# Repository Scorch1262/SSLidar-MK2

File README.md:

# SSLidar-MK2
Solid State Lidar

 Funktionen (Software V1.0) [F]:
	( Ab Board V2.0 )
- MCC UART1 Funktion
- MCC I2C Funktion
- MCC SPI Funktion
- MCC Fatfs Funktion
- Sensorauswertung 8x Time-of-Flight (VL53L0X)
- Speicherung der Sensordaten auf der SD-Karte
- Weitergabe/Verteilung von UART Signalen

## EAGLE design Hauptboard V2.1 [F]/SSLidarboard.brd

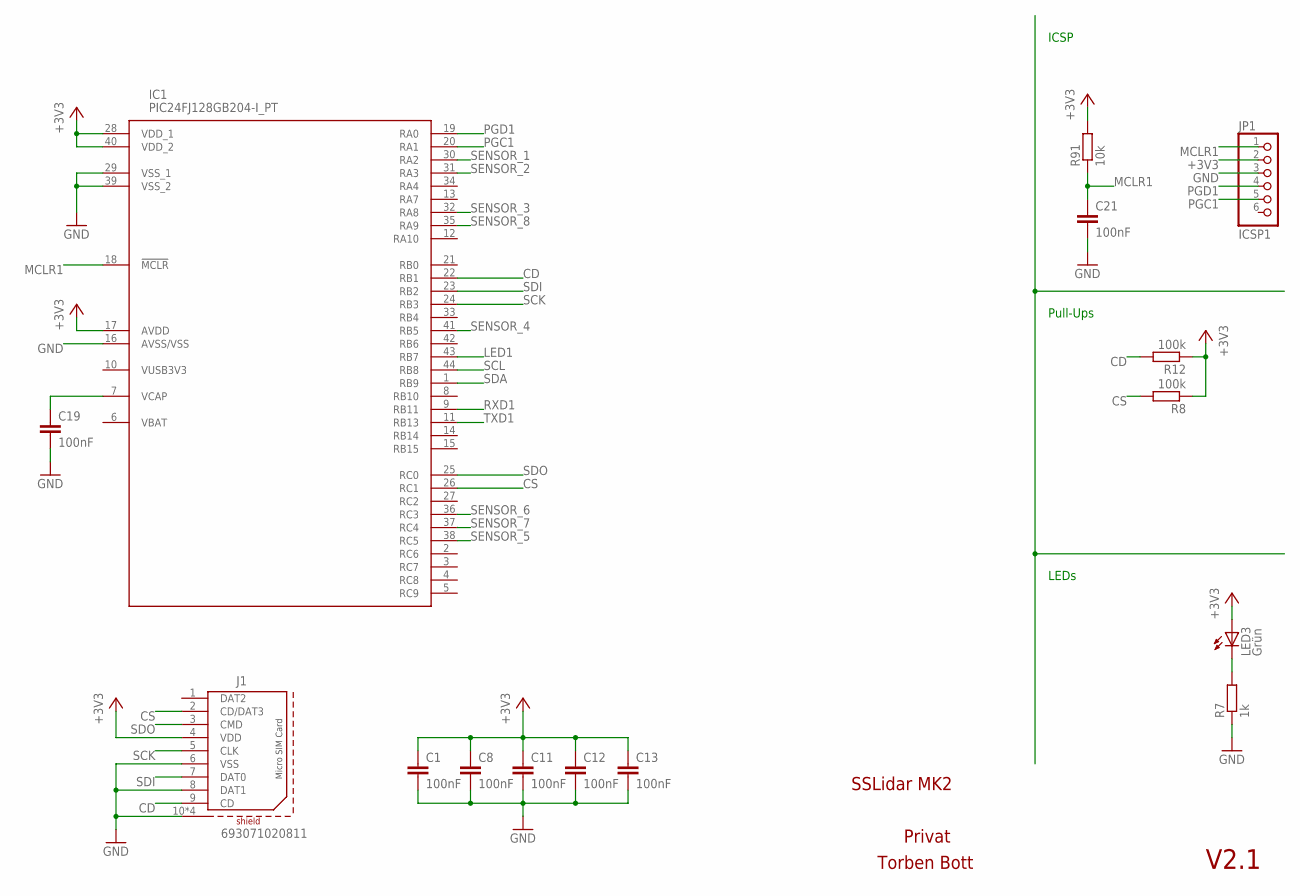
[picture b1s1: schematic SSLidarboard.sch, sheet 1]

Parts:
C1, C8, C11, C12, C13, C19, C21: 100nF; C0805
IC1: PIC24FJ128GB204-I_PT; QFP80P1200X1200X120-44N
J1: 693071020811
JP1: ICSP1; 1X06
LED3: Grün; CHIPLED_0805
R7: 1k; R0805
R8, R12: 100k; R0805
R91: 10k; R0805

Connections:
+3V3: C1.1, C8.1, C11.1, C12.1, C13.1, IC1.17 (AVDD), IC1.28 (VDD_1), IC1.40 (VDD_2), J1.4 (VDD), JP1.2, LED3.A, R8.1, R12.1, R91.2; also elsewhere on the board
CD: IC1.22 (RB1), J1.9 (CD), R12.2
CS: IC1.26 (RC1), J1.2 (CD/DAT3), R8.2
GND: C1.2, C8.2, C11.2, C12.2, C13.2, C19.2, C21.2, IC1.16 (AVSS/VSS), IC1.29 (VSS_1), IC1.39 (VSS_2), J1.6 (VSS), J1.8 (DAT1), J1.10 (SHIELD), J1.11 (SHIELD), J1.12 (SHIELD), J1.13 (SHIELD), JP1.3, R7.1; also elsewhere on the board
LED1: IC1.43 (RB7)
MCLR1: C21.1, IC1.18 (!MCLR), JP1.1, R91.1
unnamed: LED3.C, R7.2
unnamed: C19.1, IC1.7 (VCAP)
PGC1: IC1.20 (RA1), JP1.5
PGD1: IC1.19 (RA0), JP1.4
RXD1: IC1.9 (RB11); also elsewhere on the board
SCK: IC1.24 (RB3), J1.5 (CLK)
SCL: IC1.44 (RB8); also elsewhere on the board
SDA: IC1.1 (RB9); also elsewhere on the board
SDI: IC1.23 (RB2), J1.7 (DAT0)
SDO: IC1.25 (RC0), J1.3 (CMD)
SENSOR_1: IC1.30 (RA2); also elsewhere on the board
SENSOR_2: IC1.31 (RA3); also elsewhere on the board
SENSOR_3: IC1.32 (RA8); also elsewhere on the board
SENSOR_4: IC1.41 (RB5); also elsewhere on the board
SENSOR_5: IC1.38 (RC5); also elsewhere on the board
SENSOR_6: IC1.36 (RC3); also elsewhere on the board
SENSOR_7: IC1.37 (RC4); also elsewhere on the board
SENSOR_8: IC1.35 (RA9); also elsewhere on the board
TXD1: IC1.11 (RB13); also elsewhere on the board

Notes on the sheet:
SSLidar MK2
Privat
Torben Bott
V2.1
LEDs
ICSP
Pull-Ups

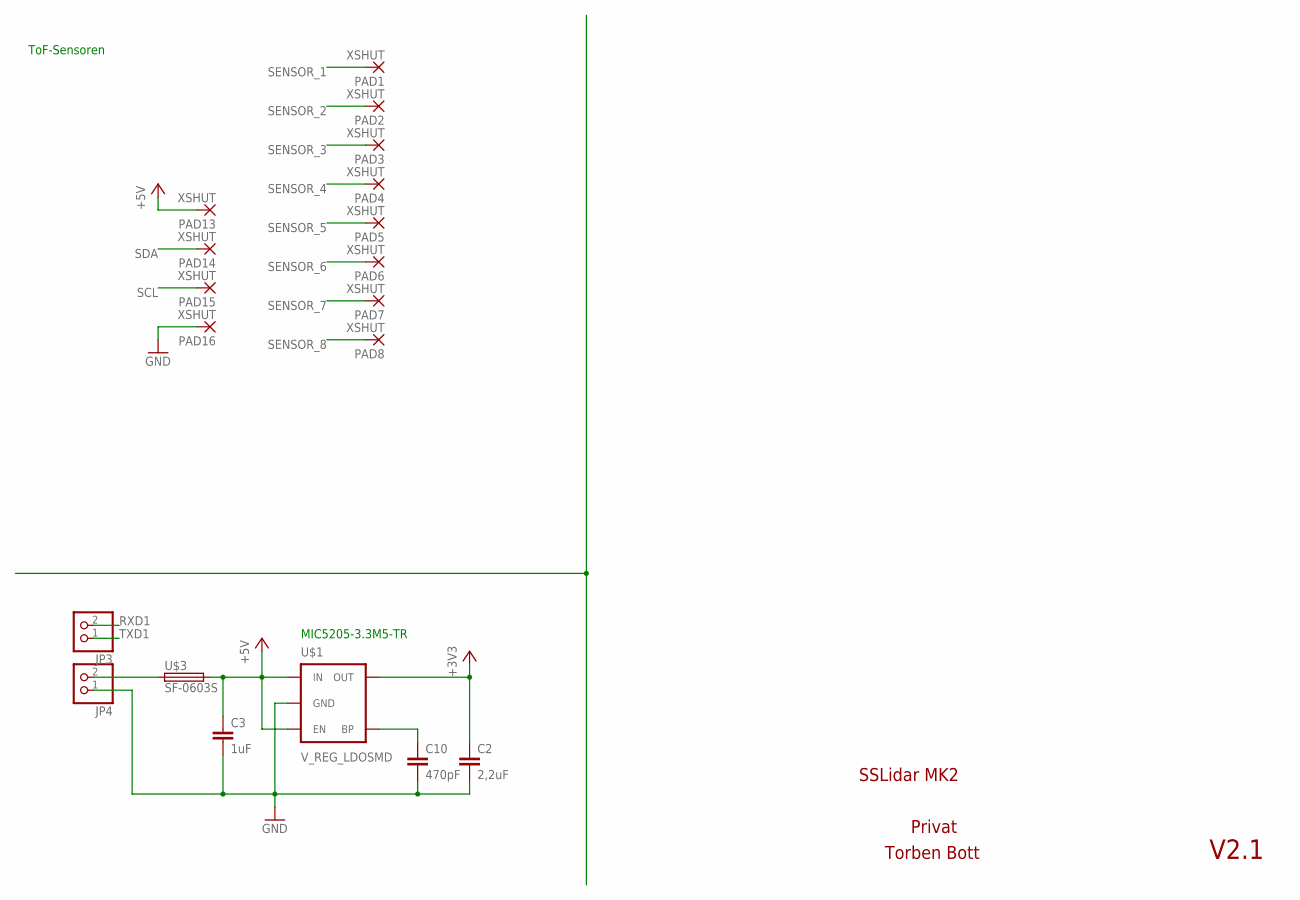
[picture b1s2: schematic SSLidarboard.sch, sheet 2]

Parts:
C2: 2,2uF; C0805
C3: 1uF; C0805
C10: 470pF; C0805
JP3, JP4: PINHD-1X2; 1X02
PAD1, PAD2, PAD3, PAD4, PAD5, PAD6, PAD7, PAD8, PAD13, PAD14, PAD15, PAD16: XSHUT; SMD1,27-2,54
U$1: V_REG_LDOSMD; SOT23-5
U$3: SF-0603S; R0603

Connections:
+3V3: C2.1, U$1.5 (OUT); also elsewhere on the board
+5V: C3.1, PAD13.1, U$1.1 (IN), U$1.3 (EN), U$3.2
GND: C2.2, C3.2, C10.2, JP4.1, PAD16.1, U$1.2 (GND); also elsewhere on the board
unnamed: JP4.2, U$3.1
unnamed: C10.1, U$1.4 (BP)
RXD1: JP3.2; also elsewhere on the board
SCL: PAD15.1; also elsewhere on the board
SDA: PAD14.1; also elsewhere on the board
SENSOR_1: PAD1.1; also elsewhere on the board
SENSOR_2: PAD2.1; also elsewhere on the board
SENSOR_3: PAD3.1; also elsewhere on the board
SENSOR_4: PAD4.1; also elsewhere on the board
SENSOR_5: PAD5.1; also elsewhere on the board
SENSOR_6: PAD6.1; also elsewhere on the board
SENSOR_7: PAD7.1; also elsewhere on the board
SENSOR_8: PAD8.1; also elsewhere on the board
TXD1: JP3.1; also elsewhere on the board

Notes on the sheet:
Privat
Torben Bott
V2.1
ToF-Sensoren
SSLidar MK2
MIC5205-3.3M5-TR

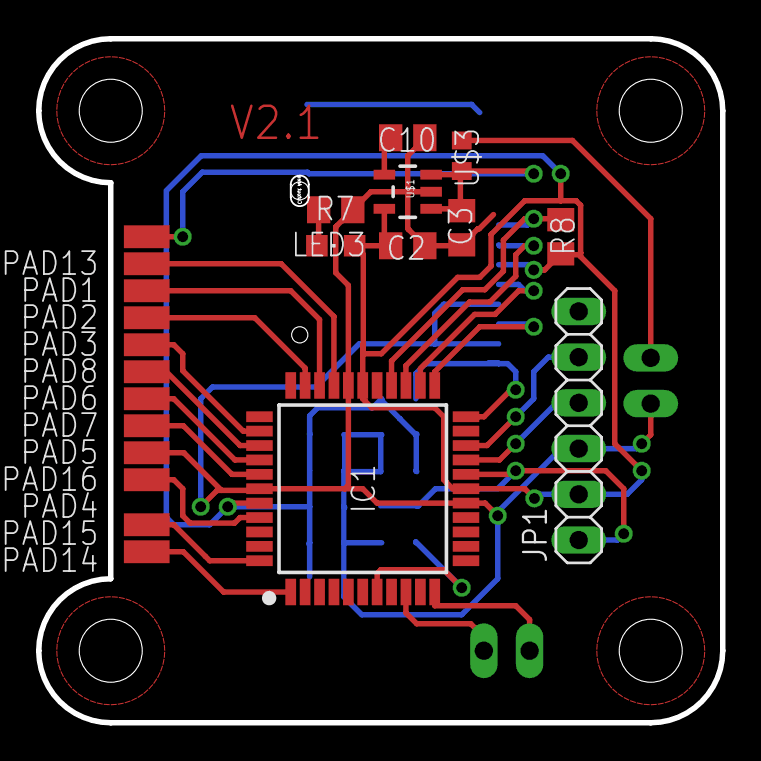
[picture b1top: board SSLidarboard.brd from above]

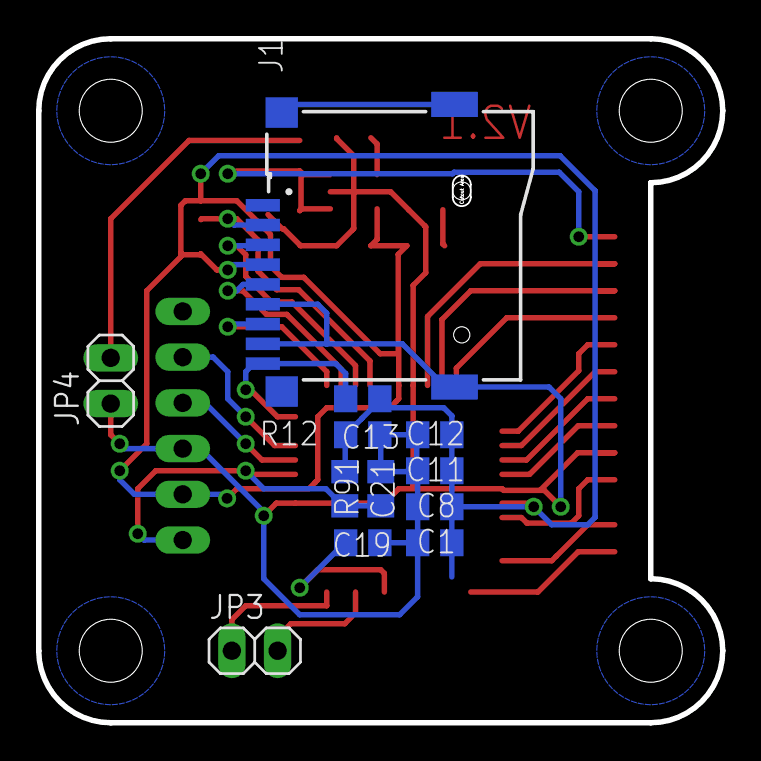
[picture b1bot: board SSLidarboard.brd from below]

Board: 2 copper layers, 38.0 x 38.0 mm, 34 parts (12 on the bottom side), 27 nets.

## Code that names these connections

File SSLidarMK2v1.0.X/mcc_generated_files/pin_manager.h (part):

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*/
/**
  @Summary
    Sets the GPIO pin, RA2, high using LATA2.

  @Description
    Sets the GPIO pin, RA2, high using LATA2.

  @Preconditions
    The RA2 must be set to an output.
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#define Sensor_01_SetHigh()          (_LATA2 = 1)
/**
  @Summary
    Sets the GPIO pin, RA2, low using LATA2.

  @Description
    Sets the GPIO pin, RA2, low using LATA2.

  @Preconditions
    The RA2 must be set to an output.
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#define Sensor_01_SetLow()           (_LATA2 = 0)
/**
  @Summary
    Toggles the GPIO pin, RA2, using LATA2.

  @Description
    Toggles the GPIO pin, RA2, using LATA2.

  @Preconditions
    The RA2 must be set to an output.
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#define Sensor_01_Toggle()           (_LATA2 ^= 1)
/**
  @Summary
    Reads the value of the GPIO pin, RA2.

  @Description
    Reads the value of the GPIO pin, RA2.

  @Preconditions
    None.
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    </code>

*/
#define Sensor_01_GetValue()         _RA2
/**
  @Summary
    Configures the GPIO pin, RA2, as an input.

  @Description
    Configures the GPIO pin, RA2, as an input.

  @Preconditions
    None.
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#define Sensor_01_SetDigitalInput()  (_TRISA2 = 1)
/**
  @Summary
    Configures the GPIO pin, RA2, as an output.

  @Description
    Configures the GPIO pin, RA2, as an output.

  @Preconditions
    None.
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#define Sensor_01_SetDigitalOutput() (_TRISA2 = 0)
/**
  @Summary
    Sets the GPIO pin, RA3, high using LATA3.

  @Description
    Sets the GPIO pin, RA3, high using LATA3.

  @Preconditions
    The RA3 must be set to an output.
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#define Sensor_02_SetHigh()          (_LATA3 = 1)
/**
  @Summary
    Sets the GPIO pin, RA3, low using LATA3.

  @Description
    Sets the GPIO pin, RA3, low using LATA3.

  @Preconditions
    The RA3 must be set to an output.
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#define Sensor_02_SetLow()           (_LATA3 = 0)
/**
  @Summary
    Toggles the GPIO pin, RA3, using LATA3.

  @Description
    Toggles the GPIO pin, RA3, using LATA3.

  @Preconditions
    The RA3 must be set to an output.
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#define Sensor_02_Toggle()           (_LATA3 ^= 1)
/**
  @Summary
    Reads the value of the GPIO pin, RA3.

  @Description
    Reads the value of the GPIO pin, RA3.

  @Preconditions
    None.
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    </code>

*/
#define Sensor_02_GetValue()         _RA3
/**
  @Summary
    Configures the GPIO pin, RA3, as an input.

  @Description
    Configures the GPIO pin, RA3, as an input.

  @Preconditions
    None.
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#define Sensor_02_SetDigitalInput()  (_TRISA3 = 1)
/**
  @Summary
    Configures the GPIO pin, RA3, as an output.

  @Description
    Configures the GPIO pin, RA3, as an output.

  @Preconditions
    None.
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#define Sensor_02_SetDigitalOutput() (_TRISA3 = 0)
/**
  @Summary
    Sets the GPIO pin, RA8, high using LATA8.

  @Description
    Sets the GPIO pin, RA8, high using LATA8.

  @Preconditions
    The RA8 must be set to an output.
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#define Sensor_03_SetHigh()          (_LATA8 = 1)
/**
  @Summary
    Sets the GPIO pin, RA8, low using LATA8.

  @Description
    Sets the GPIO pin, RA8, low using LATA8.

  @Preconditions
    The RA8 must be set to an output.
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#define Sensor_03_SetLow()           (_LATA8 = 0)
/**
  @Summary
    Toggles the GPIO pin, RA8, using LATA8.

  @Description
    Toggles the GPIO pin, RA8, using LATA8.

  @Preconditions
    The RA8 must be set to an output.
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#define Sensor_03_Toggle()           (_LATA8 ^= 1)
/**
  @Summary
    Reads the value of the GPIO pin, RA8.

  @Description
    Reads the value of the GPIO pin, RA8.

  @Preconditions
    None.
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    </code>

*/
#define Sensor_03_GetValue()         _RA8
/**
  @Summary
    Configures the GPIO pin, RA8, as an input.

  @Description
    Configures the GPIO pin, RA8, as an input.

  @Preconditions
    None.
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#define Sensor_03_SetDigitalInput()  (_TRISA8 = 1)
/**
  @Summary
    Configures the GPIO pin, RA8, as an output.

  @Description
    Configures the GPIO pin, RA8, as an output.

  @Preconditions
    None.
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#define Sensor_03_SetDigitalOutput() (_TRISA8 = 0)
/**
  @Summary
    Sets the GPIO pin, RA9, high using LATA9.

  @Description
    Sets the GPIO pin, RA9, high using LATA9.

  @Preconditions
    The RA9 must be set to an output.
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#define Sensor_08_SetHigh()          (_LATA9 = 1)
/**
  @Summary
    Sets the GPIO pin, RA9, low using LATA9.

  @Description
    Sets the GPIO pin, RA9, low using LATA9.

  @Preconditions
    The RA9 must be set to an output.
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#define Sensor_08_SetLow()           (_LATA9 = 0)
/**
  @Summary
    Toggles the GPIO pin, RA9, using LATA9.

  @Description
    Toggles the GPIO pin, RA9, using LATA9.

  @Preconditions
    The RA9 must be set to an output.
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#define Sensor_08_Toggle()           (_LATA9 ^= 1)
/**
  @Summary
    Reads the value of the GPIO pin, RA9.

  @Description
    Reads the value of the GPIO pin, RA9.

  @Preconditions
    None.
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    </code>

*/
#define Sensor_08_GetValue()         _RA9
/**
  @Summary
    Configures the GPIO pin, RA9, as an input.

  @Description
    Configures the GPIO pin, RA9, as an input.

  @Preconditions
    None.
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#define Sensor_08_SetDigitalInput()  (_TRISA9 = 1)
/**
  @Summary
    Configures the GPIO pin, RA9, as an output.

  @Description
    Configures the GPIO pin, RA9, as an output.

  @Preconditions
    None.
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#define Sensor_08_SetDigitalOutput() (_TRISA9 = 0)
/**
  @Summary
    Sets the GPIO pin, RB1, high using LATB1.

  @Description
    Sets the GPIO pin, RB1, high using LATB1.

  @Preconditions
    The RB1 must be set to an output.
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#define SDI1_SetHigh()          (_LATB1 = 1)
/**
  @Summary
    Sets the GPIO pin, RB1, low using LATB1.

  @Description
    Sets the GPIO pin, RB1, low using LATB1.

  @Preconditions
    The RB1 must be set to an output.
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#define SDI1_SetLow()           (_LATB1 = 0)
/**
  @Summary
    Toggles the GPIO pin, RB1, using LATB1.

  @Description
    Toggles the GPIO pin, RB1, using LATB1.

  @Preconditions
    The RB1 must be set to an output.
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#define SDI1_Toggle()           (_LATB1 ^= 1)
/**
  @Summary
    Reads the value of the GPIO pin, RB1.

  @Description
    Reads the value of the GPIO pin, RB1.

  @Preconditions
    None.
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    </code>

*/
#define SDI1_GetValue()         _RB1
/**
  @Summary
    Configures the GPIO pin, RB1, as an input.

  @Description
    Configures the GPIO pin, RB1, as an input.

  @Preconditions
    None.
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#define SDI1_SetDigitalInput()  (_TRISB1 = 1)
/**
  @Summary
    Configures the GPIO pin, RB1, as an output.

  @Description
    Configures the GPIO pin, RB1, as an output.

  @Preconditions
    None.
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#define SDI1_SetDigitalOutput() (_TRISB1 = 0)
/**
  @Summary
    Sets the GPIO pin, RB2, high using LATB2.

  @Description
    Sets the GPIO pin, RB2, high using LATB2.

  @Preconditions
    The RB2 must be set to an output.
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#define SCK1OUT_SetHigh()          (_LATB2 = 1)
/**
  @Summary
    Sets the GPIO pin, RB2, low using LATB2.

  @Description
    Sets the GPIO pin, RB2, low using LATB2.

  @Preconditions
    The RB2 must be set to an output.
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#define SCK1OUT_SetLow()           (_LATB2 = 0)
/**
  @Summary
    Toggles the GPIO pin, RB2, using LATB2.

  @Description
    Toggles the GPIO pin, RB2, using LATB2.

  @Preconditions
    The RB2 must be set to an output.
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#define SCK1OUT_Toggle()           (_LATB2 ^= 1)
/**
  @Summary
    Reads the value of the GPIO pin, RB2.

  @Description
    Reads the value of the GPIO pin, RB2.

  @Preconditions
    None.
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    </code>

*/
#define SCK1OUT_GetValue()         _RB2
/**
  @Summary
    Configures the GPIO pin, RB2, as an input.

  @Description
    Configures the GPIO pin, RB2, as an input.

  @Preconditions
    None.
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#define SCK1OUT_SetDigitalInput()  (_TRISB2 = 1)
/**
  @Summary
    Configures the GPIO pin, RB2, as an output.

  @Description
    Configures the GPIO pin, RB2, as an output.

  @Preconditions
    None.
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#define SCK1OUT_SetDigitalOutput() (_TRISB2 = 0)
/**
  @Summary
    Sets the GPIO pin, RB3, high using LATB3.

  @Description
    Sets the GPIO pin, RB3, high using LATB3.

  @Preconditions
    The RB3 must be set to an output.
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#define SDO1_SetHigh()          (_LATB3 = 1)
/**
  @Summary
    Sets the GPIO pin, RB3, low using LATB3.

  @Description
    Sets the GPIO pin, RB3, low using LATB3.

  @Preconditions
    The RB3 must be set to an output.
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#define SDO1_SetLow()           (_LATB3 = 0)
/**
  @Summary
    Toggles the GPIO pin, RB3, using LATB3.

  @Description
    Toggles the GPIO pin, RB3, using LATB3.

  @Preconditions
    The RB3 must be set to an output.
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#define SDO1_Toggle()           (_LATB3 ^= 1)
/**
  @Summary
    Reads the value of the GPIO pin, RB3.

  @Description
    Reads the value of the GPIO pin, RB3.

  @Preconditions
    None.
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    </code>

*/
#define SDO1_GetValue()         _RB3
/**
  @Summary
    Configures the GPIO pin, RB3, as an input.

  @Description
    Configures the GPIO pin, RB3, as an input.

  @Preconditions
    None.
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#define SDO1_SetDigitalInput()  (_TRISB3 = 1)
/**
  @Summary
    Configures the GPIO pin, RB3, as an output.

  @Description
    Configures the GPIO pin, RB3, as an output.

  @Preconditions
    None.
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#define SDO1_SetDigitalOutput() (_TRISB3 = 0)
/**
  @Summary
    Sets the GPIO pin, RB5, high using LATB5.
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

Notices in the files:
SSLidarMK2v1.0.X/mcc_generated_files/pin_manager.h:
(c) 2020 Microchip Technology Inc. and its subsidiaries. You may use this
parts and their libraries:
693071020811: Copyright: Würth Elektronik
